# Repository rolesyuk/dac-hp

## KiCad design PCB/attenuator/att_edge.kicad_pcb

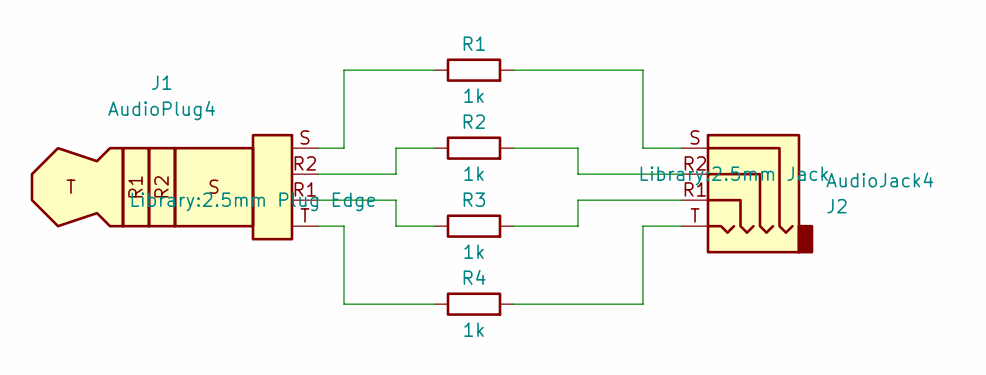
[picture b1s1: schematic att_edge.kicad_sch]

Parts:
J1: AudioPlug4; 2.5mm Plug Edge
J2: AudioJack4; 2.5mm Jack
R1, R2, R3, R4: 1k; R_0603_1608Metric

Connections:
unnamed: J1.R1, R3.1
unnamed: J1.R2, R2.1
unnamed: J1.S, R1.1
unnamed: J1.T, R4.1
unnamed: J2.R1, R3.2
unnamed: J2.R2, R2.2
unnamed: J2.S, R1.2
unnamed: J2.T, R4.2

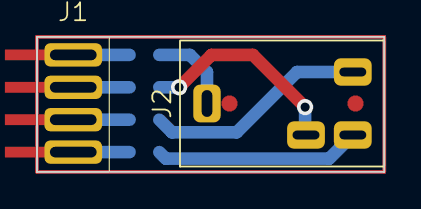
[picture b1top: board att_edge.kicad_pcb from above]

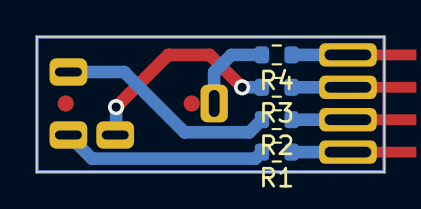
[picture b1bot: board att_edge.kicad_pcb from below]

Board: 2 copper layers, 19.3 x 7.5 mm, 6 parts (4 on the bottom side), 8 nets.

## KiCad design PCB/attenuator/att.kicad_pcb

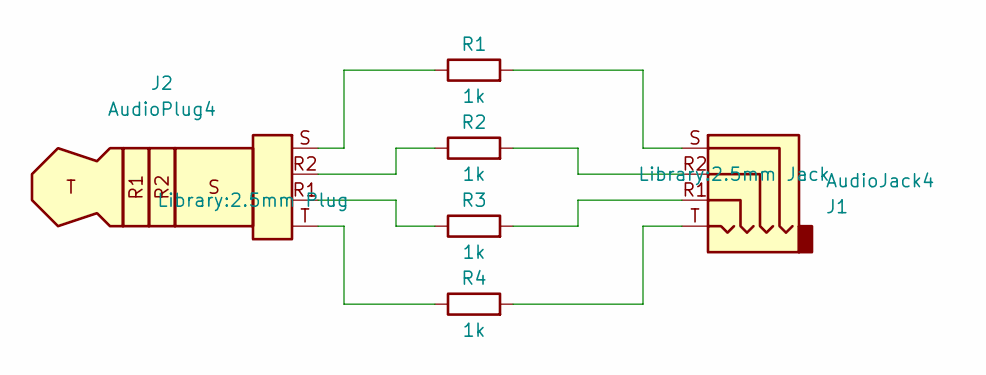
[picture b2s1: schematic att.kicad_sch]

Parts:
J1: AudioJack4; 2.5mm Jack
J2: AudioPlug4; 2.5mm Plug
R1, R2, R3, R4: 1k; R_0603_1608Metric

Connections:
unnamed: J1.R1, R3.2
unnamed: J1.R2, R2.2
unnamed: J1.S, R1.2
unnamed: J1.T, R4.2
unnamed: J2.R1, R3.1
unnamed: J2.R2, R2.1
unnamed: J2.S, R1.1
unnamed: J2.T, R4.1

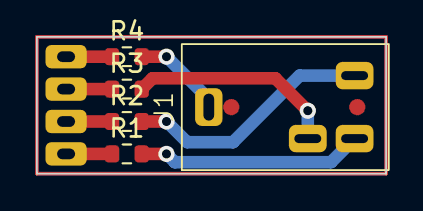
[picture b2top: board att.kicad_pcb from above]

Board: 2 copper layers, 19.4 x 7.6 mm, 6 parts (1 on the bottom side), 8 nets.

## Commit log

2024-06-19 Updated attenuator designs
2024-08-07 Updated filter design to better fit paper sheets
2025-01-09 Added magnet case
2025-01-11 Reduced magnet holder size
2025-02-07 Updated 9039s firmwares (no-pop + PTL)
2025-03-04 Added headband design
2025-03-04 Increased headband size for Hifiman Edition XS
2025-03-09 Added full 3D printed headband design
2025-03-12 Updated headband 3D design
2025-05-21 Added 9038 USB cable fix
2025-06-05 Updated 9038s firmwares
